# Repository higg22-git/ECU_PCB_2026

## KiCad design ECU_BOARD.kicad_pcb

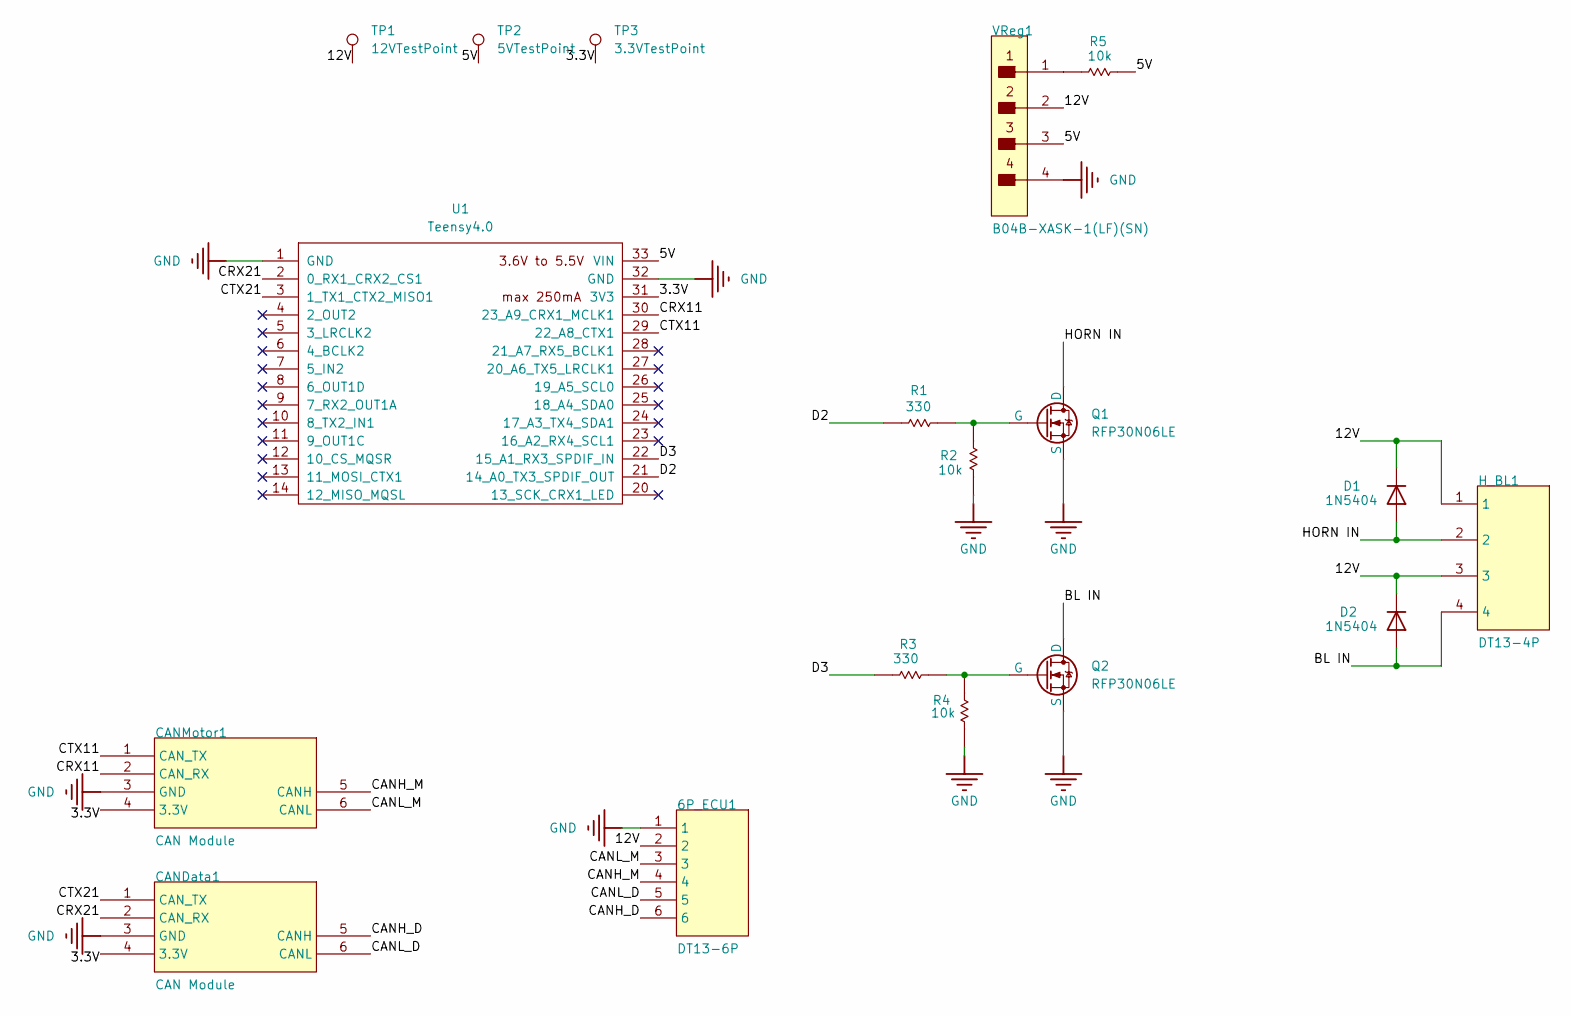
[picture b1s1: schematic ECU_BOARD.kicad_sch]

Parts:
6P_ECU1: DT13-6P; 6PinDeutch
CANData1: CAN Module; CAN_Module
CANMotor1: CAN Module; CAN_Module
D1, D2: 1N5404; D_DO-201AD_P15.24mm_Horizontal
H_BL1: DT13-4P; 4pinDeutch
Q1, Q2: RFP30N06LE; TO-220-3_Vertical
R1, R3: 330; R_Axial_DIN0207_L6.3mm_D2.5mm_P10.16mm_Horizontal; VOLTAGE RATING 250V; VOLTAGE RATING (DC) 200V
R2, R4, R5: 10k; R_Axial_DIN0207_L6.3mm_D2.5mm_P10.16mm_Horizontal; VOLTAGE RATING 250V; VOLTAGE RATING (DC) 200V
TP1: 12VTestPoint; TestPoint_THTPad_2.0x2.0mm_Drill1.0mm
TP2: 5VTestPoint; TestPoint_THTPad_2.0x2.0mm_Drill1.0mm
TP3: 3.3VTestPoint; TestPoint_THTPad_2.0x2.0mm_Drill1.0mm
U1: Teensy4.0; Teensy40
VReg1: B04B-XASK-1(LF)(SN); PinSocket_1x04_P2.54mm_Vertical; CURRENT RATING 3A; VOLTAGE RATING 250V; MANUFACTURER PART NUMBER B04B-XASK-1(LF)(SN); DIGIKEY DESCRIPTION CONN HEADER VERT 4POS 2.5MM

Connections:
/3.3V: CANData1.4 (3.3V), CANMotor1.4 (3.3V), TP3.1, U1.31 (3V3)
/5V: R5.2, TP2.1, U1.33 (VIN), VReg1.3
/12V: 6P_ECU1.2, D1.1 (K), D2.1 (K), H_BL1.1, H_BL1.3, TP1.1, VReg1.2
/BL IN: D2.2 (A), H_BL1.4, Q2.2 (D)
/CANH_D: 6P_ECU1.6, CANData1.5 (CANH)
/CANH_M: 6P_ECU1.4, CANMotor1.5 (CANH)
/CANL_D: 6P_ECU1.5, CANData1.6 (CANL)
/CANL_M: 6P_ECU1.3, CANMotor1.6 (CANL)
/CRX11: CANMotor1.2 (CAN_RX), U1.30 (23_A9_CRX1_MCLK1)
/CRX21: CANData1.2 (CAN_RX), U1.2 (0_RX1_CRX2_CS1)
/CTX11: CANMotor1.1 (CAN_TX), U1.29 (22_A8_CTX1)
/CTX21: CANData1.1 (CAN_TX), U1.3 (1_TX1_CTX2_MISO1)
/D2: R1.2, U1.21 (14_A0_TX3_SPDIF_OUT)
/D3: R3.2, U1.22 (15_A1_RX3_SPDIF_IN)
/HORN IN: D1.2 (A), H_BL1.2, Q1.2 (D)
GND: 6P_ECU1.1, CANData1.3 (GND), CANMotor1.3 (GND), Q1.3 (S), Q2.3 (S), R2.1, R4.1, U1.1 (GND), U1.32 (GND), VReg1.4
unnamed: Q1.1 (G), R1.1, R2.2
unnamed: Q2.1 (G), R3.1, R4.2
unnamed: R5.1, VReg1.1

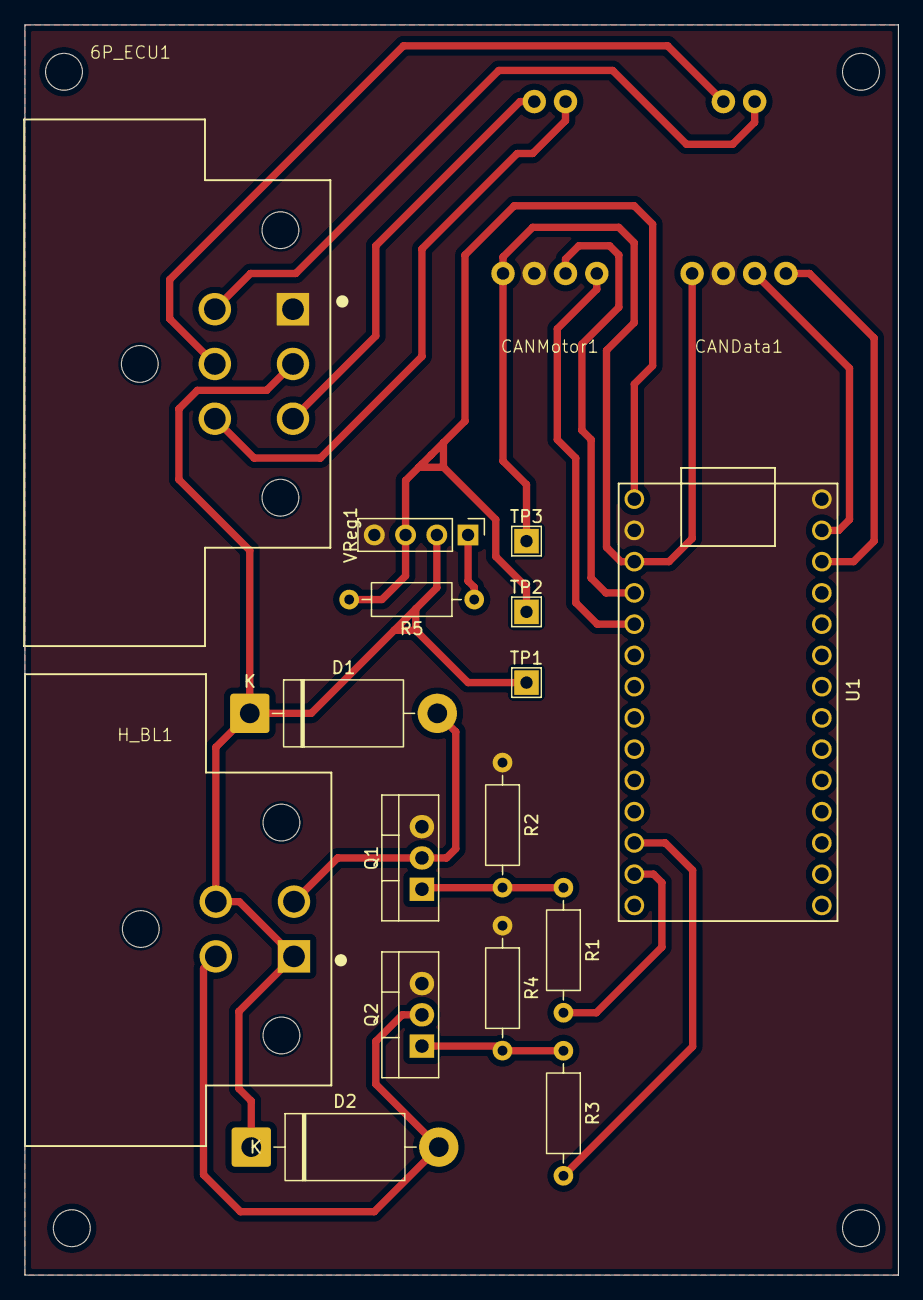
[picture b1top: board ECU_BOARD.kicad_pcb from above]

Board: 2 copper layers, 71.0 x 101.6 mm, 18 parts (0 on the bottom side), 19 nets.

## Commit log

2026-03-10 second commit
2026-03-11 finished
